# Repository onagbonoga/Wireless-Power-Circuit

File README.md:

# wireless_power_circuit

Planning on using: 28 AWG magnet wire.
http://www.tesla-institute.com/!app/sim/fscic.php

Coil ID: 30 mm
Number of Turns: 50
Wire diameter used: 0.32 mm
Spacing between turns: 0.05 mm (very rough guess)

Inductance (L): 145.61 uH (Theoretical)
Coil OD: 67 mm
Wire length: 7.618 m

Inductance (L): 417.5 uH (Practical - E05 measurements)

Capacitor parameters: 500 mm length x width of foil tape (~50mm).
Capacitor dielectric: wax paper (unknown permitivity).

Measured capacitance: ~9.3 nF

Resonant frequency (1/(2*pi*sqrt(L*C))): ~136.77 kHz (Based on theoretical L)
Resonant frequency (1/(2*pi*sqrt(L*C))): ~80.77 kHz (Based on measured L - E05)
Resonant frequency (measured) = ??

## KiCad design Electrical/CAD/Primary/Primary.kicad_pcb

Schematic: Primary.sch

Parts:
BT1: 2x_Battery_Cell; Keystone_Dual_AA_Holder
C1, C2: 10nF; C_Disc_D6.0mm_W2.5mm_P5.00mm
C3: 470pF; C_Disc_D6.0mm_W2.5mm_P5.00mm
C4: C; C_Disc_D6.0mm_W2.5mm_P5.00mm
L1: L; CoilSpiral_25_Bezier
Q1: 2N3904; TO-92_Inline
Q2: 2N3906; TO-92_Inline
R1: 33k; R_Axial_DIN0207_L6.3mm_D2.5mm_P7.62mm_Horizontal
R2: 1M; R_Axial_DIN0207_L6.3mm_D2.5mm_P7.62mm_Horizontal
R3: 2.2k; R_Axial_DIN0207_L6.3mm_D2.5mm_P7.62mm_Horizontal
R4: 5.1; R_Axial_DIN0207_L6.3mm_D2.5mm_P7.62mm_Horizontal
SW1: SW_DPST; GF-325
U1: LMC555xN; DIP-8_W7.62mm
U2: MCP6282

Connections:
+1V5: C4.2, L1.2, SW1.2, U2.3
+3V0: Q1.3 (C), R2.1, SW1.4, U1.4, U1.8, U2.8
GND: BT1.3 (-), C1.2, C2.2, Q2.3 (C), U1.1, U2.4
unnamed: BT1.1 (+), SW1.3
unnamed: BT1.2 (+), BT1.4 (-), SW1.1
unnamed: C1.1, U1.5
unnamed: C2.1, R1.2, R2.2, U1.2, U1.6
unnamed: C3.1, U2.1, U2.5
unnamed: C3.2, R3.1, U2.2
unnamed: C4.1, L1.1, R4.2
unnamed: Q1.1 (E), Q2.1 (E), R4.1, U2.6
unnamed: Q1.2 (B), Q2.2 (B), U2.7
unnamed: R1.1, R3.2, U1.3

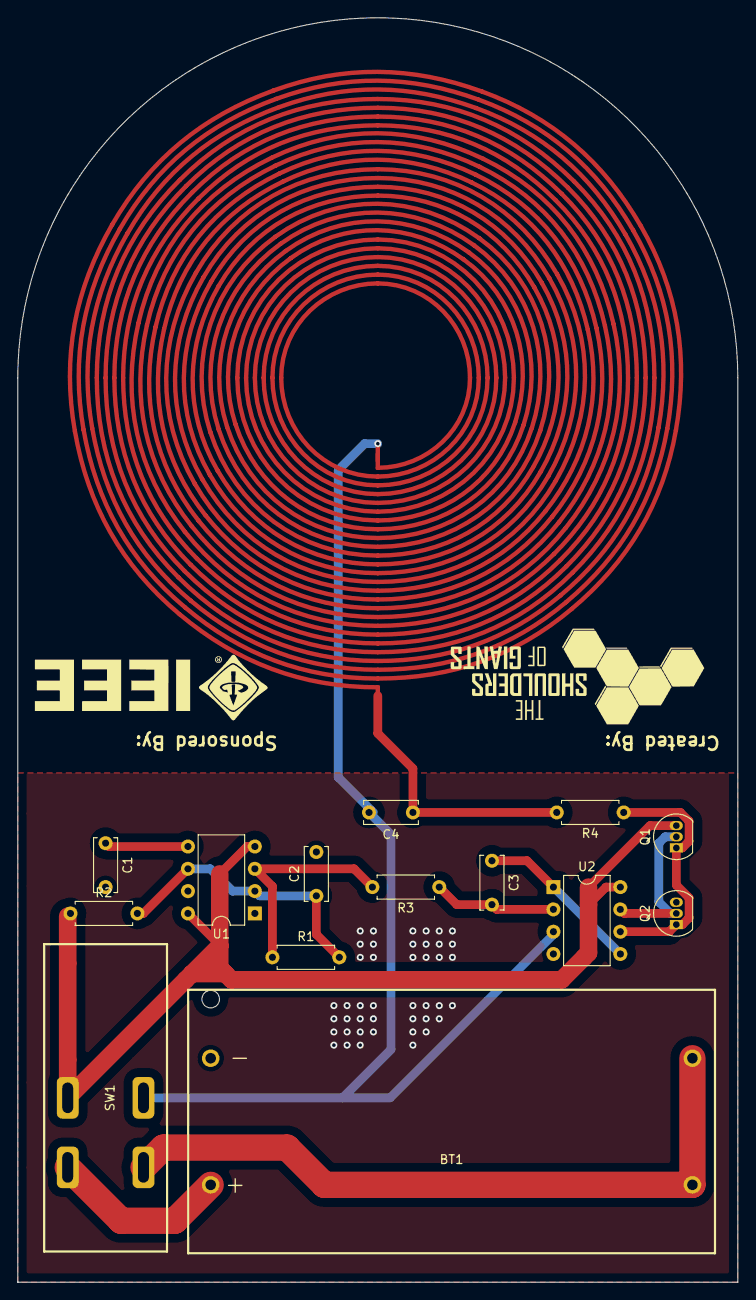
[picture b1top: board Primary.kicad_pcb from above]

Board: 2 copper layers, 82.0 x 144.0 mm, 15 parts (0 on the bottom side), 13 nets.

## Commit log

2019-11-30 End of Episode 03.
2019-11-30 Added CAM files.
2019-12-07 Mid episode 04 commit.
2019-12-07 End of episode 04 commit.
2019-12-07 Small post-E04 commit.
2019-12-14 Pre-episode 5 updates.
2019-12-14 Rounded spacing nubs on base plate.
2019-12-14 End of Episode 05.
2019-12-16 Modifications to improve wire spooling.
2020-01-19 End of episode 6.
2020-01-26 End of Episode 7.
2020-02-16 Mid episode 10 commit.
2020-02-17 End of episode 10 commit.
2020-02-17 ADD spiral-component-plugin.py and 2 versions of generated spiral coil components (with bezier curves and with straight lines).
    The plugin cannot be used in Kicad without applying a trivial patch (+3 lines) which I will submit to kicad soon.
    The straight lines version should be compatible with the latest stable release (5.1.5).
    The bezier curves version should be compatible with the latest Nightly Development Builds from https://kicad-downloads.s3.cern.ch/index.html?prefix=windows/nightly/.
    However it will be very very slow to load (>15 minutes). I also have a patch for this issue that I will also submit.
2020-02-17 Update the PCB using the bezier curve spiral coil component. See primary-pcb-coil-bezier.png for a preview of the result.
    It requires using the latest Nightly Development Builds from https://kicad-downloads.s3.cern.ch/index.html?prefix=windows/nightly/.
    However, as noted in the previous commit, it will be very very slow to load (>15 minutes).
    I have a patch for this issue that I will submit.
    In the meantime, if anyone is interested to use this please contact me and I will send it to you.
2020-02-17 Merging spiral-component changes into master.
2020-02-18 Generated Gerber files.
2020-02-23 Modified housing and added 3D models to PCB.
2020-02-27 Updated GCode_Files
2020-02-27 Updated g-code batch filenames.
2020-02-29 Minor CAD / CAM updates.
2020-02-29 Modified footprints for caps and battery on primary PCB.
2020-02-29 PCB: fix route to new capacitor footprints
2020-02-29 PCB: change pads for switch to slots
2020-02-29 PCB: fix remaining tracks that were too close to pins, make slots for switch .25mm longer
2020-02-29 End of Episode 12.
2020-03-05 graphics
2020-04-24 Added video and relevant files
2020-04-24 updated video
